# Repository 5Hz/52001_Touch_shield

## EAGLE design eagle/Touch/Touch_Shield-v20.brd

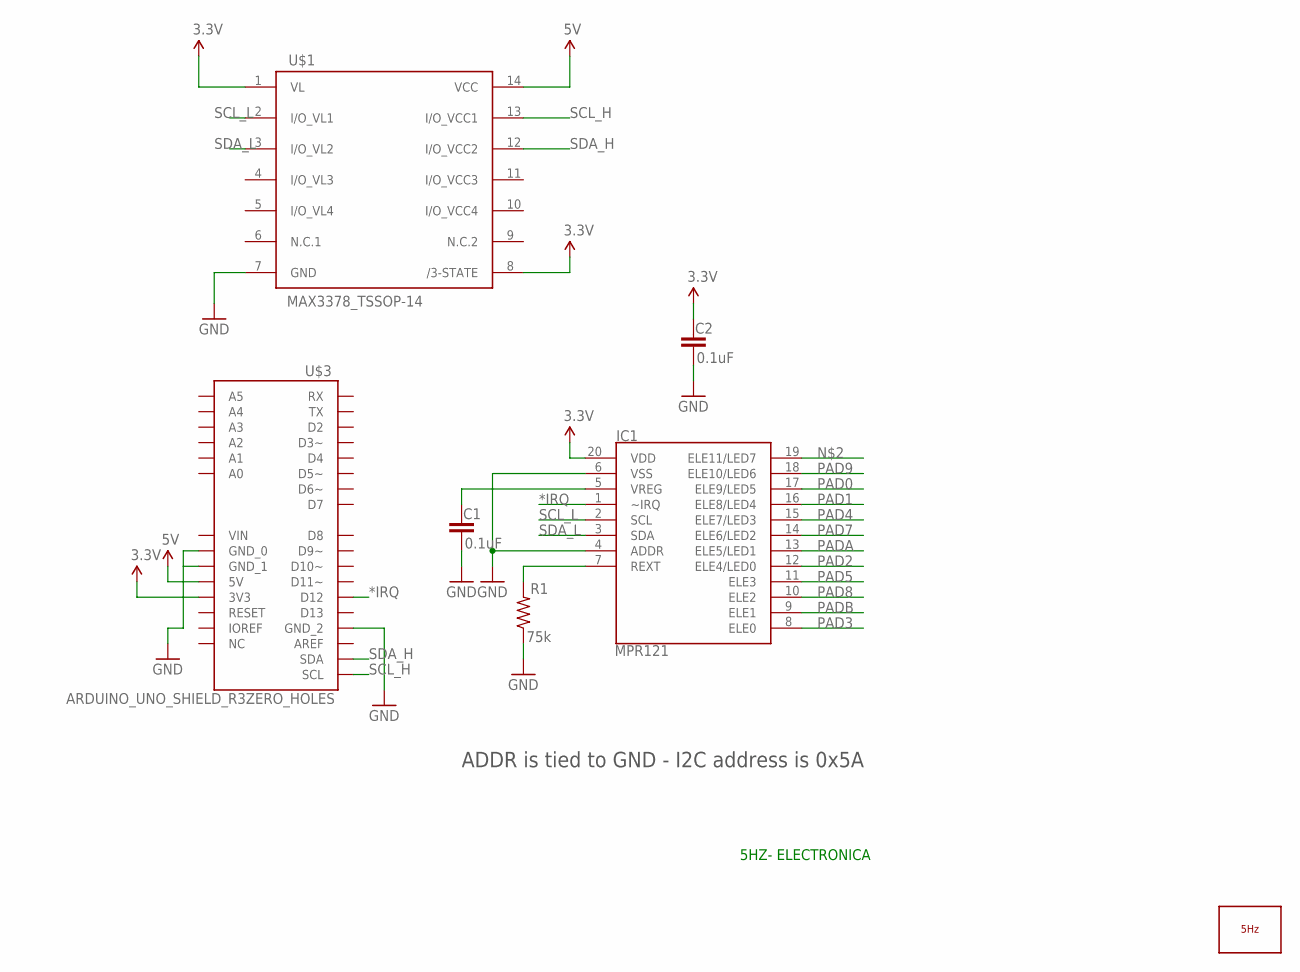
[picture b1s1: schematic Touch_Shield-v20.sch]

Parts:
C1, C2: 0.1uF; 0402-CAP
IC1: MPR121; QFN-20-0.4MM
LOGO1: LOGO_5HZ_H_10MM; 5HZ_LOGO_H_10MM
R1: 75k; 0402-RES
U$1: MAX3378_TSSOP-14; TSSOP14
U$3: ARDUINO_UNO_SHIELD_R3ZERO_HOLES; UNO_R3_SHIELD_NO_SILK

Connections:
3.3V: C2.1, IC1.20 (VDD), U$1.1 (VL), U$1.8 (/3-STATE), U$3.3.3V (3V3)
5V: U$1.14 (VCC), U$3.5V
*IRQ: IC1.1 (~IRQ), U$3.D12
GND: C1.2, C2.2, IC1.4 (ADDR), IC1.6 (VSS), R1.1, U$1.7 (GND), U$3.GND_0, U$3.GND_1, U$3.GND_2
PAD0: IC1.17 (ELE9/LED5)
PAD1: IC1.16 (ELE8/LED4)
PAD2: IC1.12 (ELE4/LED0)
PAD3: IC1.8 (ELE0)
PAD4: IC1.15 (ELE7/LED3)
PAD5: IC1.11 (ELE3)
PAD7: IC1.14 (ELE6/LED2)
PAD8: IC1.10 (ELE2)
PAD9: IC1.18 (ELE10/LED6)
PADA: IC1.13 (ELE5/LED1)
PADB: IC1.9 (ELE1)
REXT: IC1.7 (REXT), R1.2
SCL_H: U$1.13 (I/O_VCC1), U$3.SCL
SCL_L: IC1.2 (SCL), U$1.2 (I/O_VL1)
SDA_H: U$1.12 (I/O_VCC2), U$3.SDA
SDA_L: IC1.3 (SDA), U$1.3 (I/O_VL2)
VREG: C1.1, IC1.5 (VREG)

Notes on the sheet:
ADDR is tied to GND - I2C address is 0x5A
5HZ- ELECTRONICA

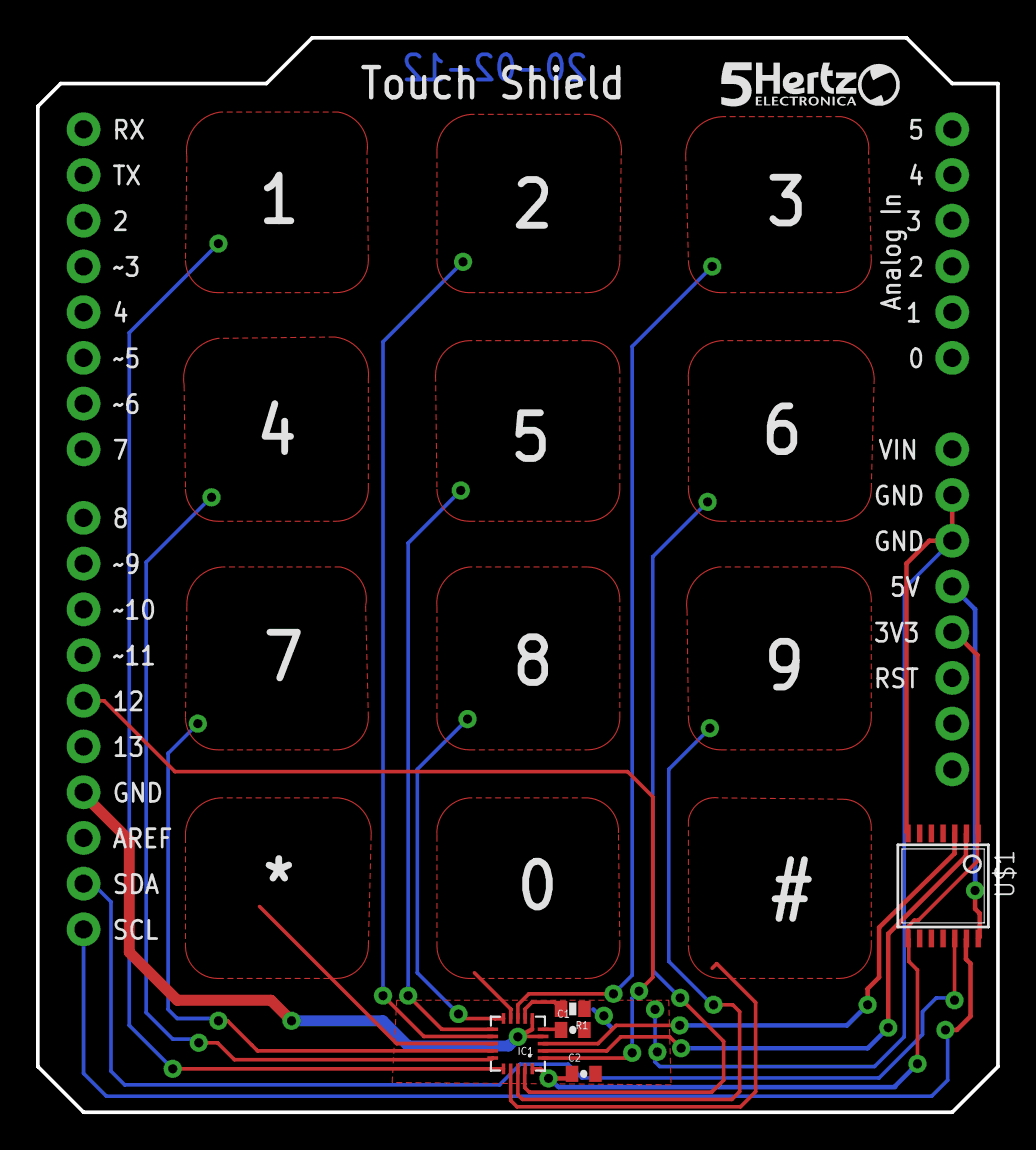
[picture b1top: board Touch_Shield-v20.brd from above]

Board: 2 copper layers, 53.3 x 59.7 mm, 7 parts (0 on the bottom side), 10 nets.

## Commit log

2014-01-15 Creacion
